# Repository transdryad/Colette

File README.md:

# Colette

A keyboard designed to be ergonomic, clean, convenient, maintainable, and versatile.
It is optimized for English, but can type every character supported by the US International layout (though it's not followed or fully required for basic usage.)
By default, it uses Colemak Mod-DH with a few changes to punctuation.

I made this keyboard to get more experience building hardware and enable a more cohesive coding environment.
I also wanted it to be good at typing text as well and have support for similar languages to english like French,
Spanish, and German.

* Keyboard Maintainer: [Hazel Viswanath](https://github.com/transdryad)
* Hardware Supported: Colette PCB, RPi/Orpheus Pico v1, Cherry MX keys, standard TRS jack

# Software used:
Kicad, Pycharm, FreeCAD, QMK, and Keyboard-Layout-Editor.com

# Firmware:
To compile & flash formware, install qmk system-wide and run bf.sh.
When it's "waiting for drive," plug in while pressing the BOOTSEL button on the PICO.
WARNING: the script will delete qmk firmware monorepo tree.
Backup any changes.

# BOM

BOM also in BOM.csv

| Part                      | Quantity | Proposed Sourcing?                                                                            |
|:--------------------------|:---------|:----------------------------------------------------------------------------------------------|
| PCBs                      | 2        | https://jlcpcb.com                                                                            |
| KeySwitches               | 58       | https://mechanicalkeyboards.com/products/cherry-mx2a-brown-55g-tactile?variant=48020838351148 |
| Keycaps                   | ~58      | https://www.amazon.com/YMDK-Profile-Keyset-Mechanical-Keyboard/dp/B07S18VCDN?th=1             |
| 1N4148 Diodes             | 58       | https://www.digikey.com/en/products/detail/onsemi/1N4148/458603                               |
| TRS Jacks                 | 2        | https://www.digikey.com/en/products/detail/same-sky-formerly-cui-devices/SJ1-3523N/738689     |
| TRS Cables                | 1        | https://www.mycablemart.com/store/cart.php?m=product_detail&p=9040                            |
| Orpheus Picos             | 2        | HQ?                                                                                           |
| M3x16mm Screws            | 8        | ?                                                                                             |
| M3x5mx4mm headset inserts | 8        | ?                                                                                             |
| Case                      | 4 parts  | Printing legion?                                                                              |

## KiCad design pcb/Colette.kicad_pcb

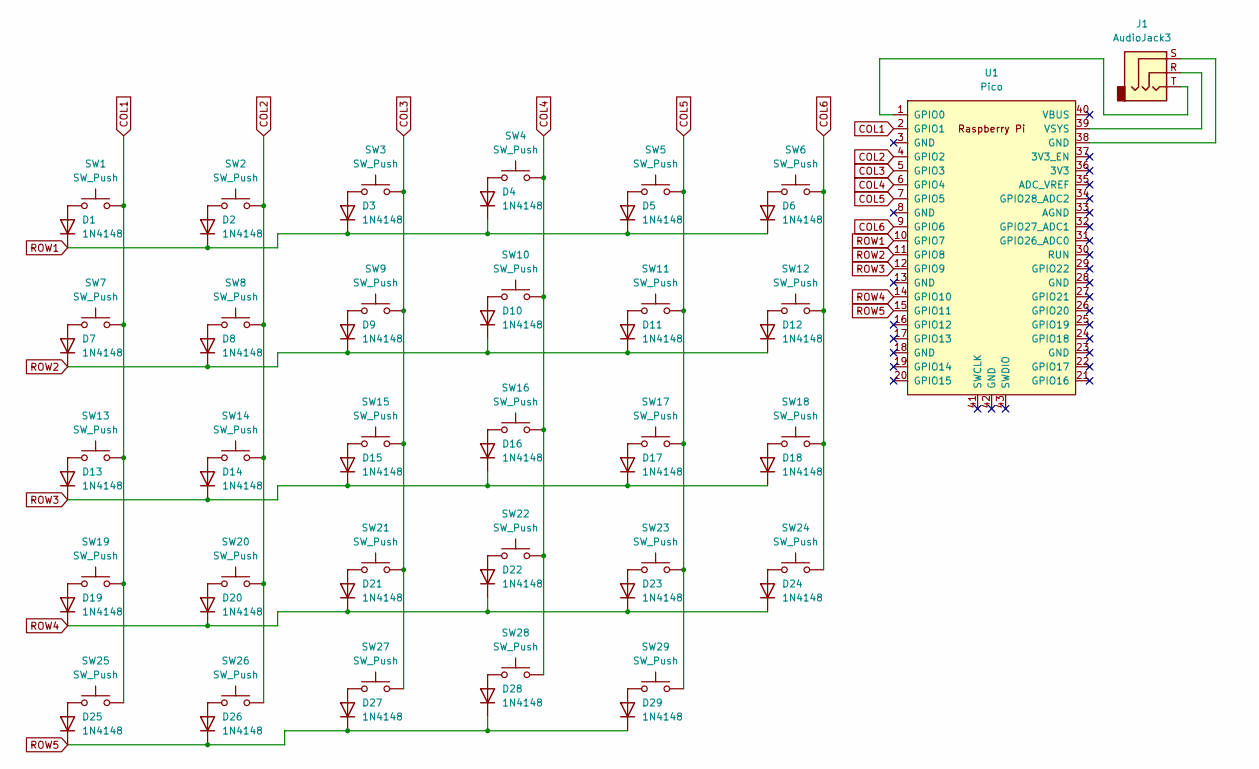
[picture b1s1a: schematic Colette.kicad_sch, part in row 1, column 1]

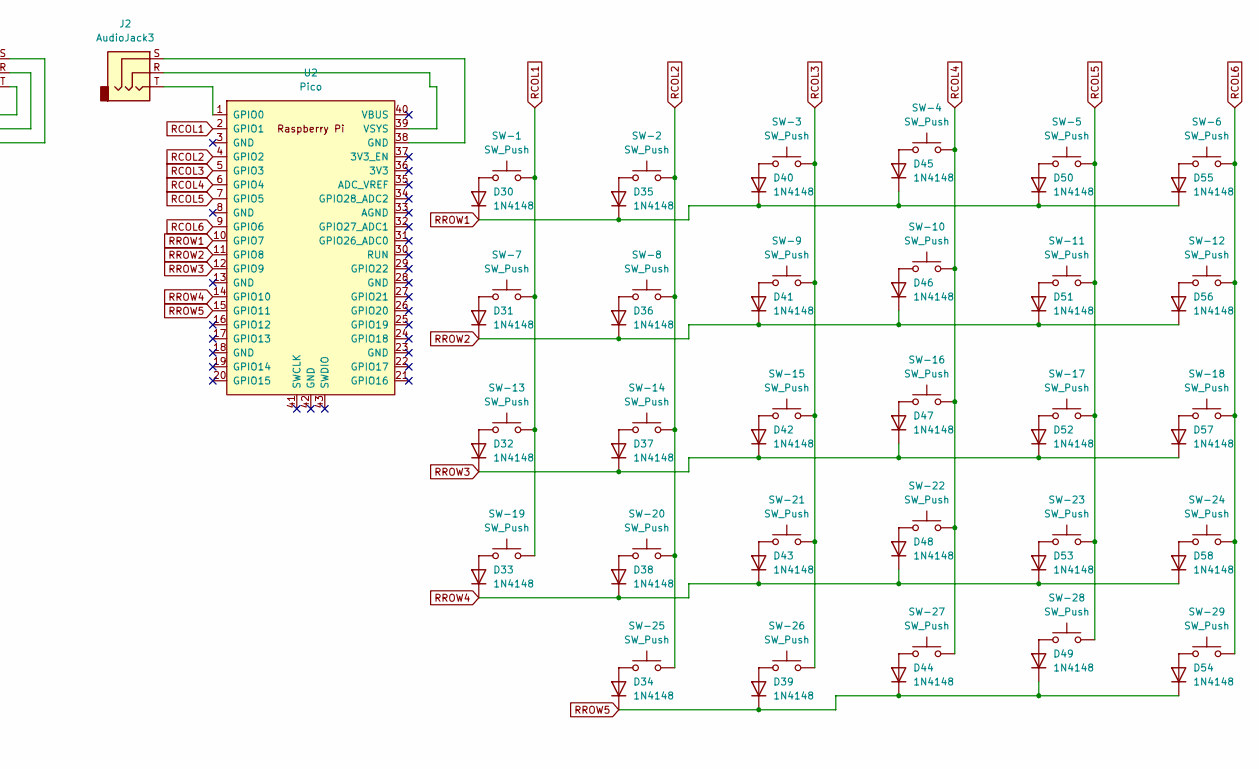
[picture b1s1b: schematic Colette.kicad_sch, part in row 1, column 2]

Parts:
D1, D2, D3, D4, D5, D6, D7, D8, D9, D10, D11, D12, D13, D14, D15, D16, D17, D18, D19, D20, D21, D22, D23, D24, D25, D26, D27, D28, D29, D30, D31, D32, D33, D34, D35, D36, D37, D38, D39, D40, D41, D42, D43, D44, D45, D46, D47, D48, D49, D50, D51, D52, D53, D54, D55, D56, D57, D58: 1N4148; D_DO-35_SOD27_P7.62mm_Horizontal
J1, J2: AudioJack3; Jack_3.5mm_CUI_SJ1-3523N_Horizontal
SW1, SW2, SW3, SW4, SW5, SW6, SW7, SW8, SW9, SW10, SW11, SW12, SW13, SW14, SW15, SW16, SW17, SW18, SW19, SW20, SW21, SW22, SW23, SW24, SW25, SW26, SW27, SW28: SW_Push; SW_Cherry_MX_1.00u_PCB
SW29: SW_Push; SW_Cherry_MX_2.00u_PCB
SW-1, SW-2, SW-3, SW-4, SW-5, SW-6, SW-7, SW-8, SW-9, SW-10, SW-11, SW-12, SW-13, SW-14, SW-15, SW-16, SW-17, SW-18, SW-19, SW-20, SW-21, SW-22, SW-23, SW-24, SW-26, SW-27, SW-28, SW-29: SW_Push; SW_Cherry_MX_1.00u_PCB
SW-25: SW_Push; SW_Cherry_MX_2.00u_PCB
U1, U2: Pico; RaspberryPi_Pico_Common_THT

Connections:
COL1: SW1.2, SW7.2, SW13.2, SW19.2, SW25.2, U1.2 (GPIO1)
COL2: SW2.2, SW8.2, SW14.2, SW20.2, SW26.2, U1.4 (GPIO2)
COL3: SW3.2, SW9.2, SW15.2, SW21.2, SW27.2, U1.5 (GPIO3)
COL4: SW4.2, SW10.2, SW16.2, SW22.2, SW28.2, U1.6 (GPIO4)
COL5: SW5.2, SW11.2, SW17.2, SW23.2, SW29.2, U1.7 (GPIO5)
COL6: SW6.2, SW12.2, SW18.2, SW24.2, U1.9 (GPIO6)
unnamed: D1.2 (A), SW1.1
unnamed: D2.2 (A), SW2.1
unnamed: D3.2 (A), SW3.1
unnamed: D4.2 (A), SW4.1
unnamed: D5.2 (A), SW5.1
unnamed: D6.2 (A), SW6.1
unnamed: D7.2 (A), SW7.1
unnamed: D8.2 (A), SW8.1
unnamed: D9.2 (A), SW9.1
unnamed: D10.2 (A), SW10.1
unnamed: D11.2 (A), SW11.1
unnamed: D12.2 (A), SW12.1
unnamed: D13.2 (A), SW13.1
unnamed: D14.2 (A), SW14.1
unnamed: D15.2 (A), SW15.1
unnamed: D16.2 (A), SW16.1
unnamed: D17.2 (A), SW17.1
unnamed: D18.2 (A), SW18.1
unnamed: D19.2 (A), SW19.1
unnamed: D20.2 (A), SW20.1
unnamed: D21.2 (A), SW21.1
unnamed: D22.2 (A), SW22.1
unnamed: D23.2 (A), SW23.1
unnamed: D24.2 (A), SW24.1
unnamed: D25.2 (A), SW25.1
unnamed: D26.2 (A), SW26.1
unnamed: D27.2 (A), SW27.1
unnamed: D28.2 (A), SW28.1
unnamed: D29.2 (A), SW29.1
unnamed: D30.2 (A), SW-1.1
unnamed: D31.2 (A), SW-7.1
unnamed: D32.2 (A), SW-13.1
unnamed: D33.2 (A), SW-19.1
unnamed: D34.2 (A), SW-25.1
unnamed: D35.2 (A), SW-2.1
unnamed: D36.2 (A), SW-8.1
unnamed: D37.2 (A), SW-14.1
unnamed: D38.2 (A), SW-20.1
unnamed: D39.2 (A), SW-26.1
unnamed: D40.2 (A), SW-3.1
unnamed: D41.2 (A), SW-9.1
unnamed: D42.2 (A), SW-15.1
unnamed: D43.2 (A), SW-21.1
unnamed: D44.2 (A), SW-27.1
unnamed: D45.2 (A), SW-4.1
unnamed: D46.2 (A), SW-10.1
unnamed: D47.2 (A), SW-16.1
unnamed: D48.2 (A), SW-22.1
unnamed: D49.2 (A), SW-28.1
unnamed: D50.2 (A), SW-5.1
unnamed: D51.2 (A), SW-11.1
unnamed: D52.2 (A), SW-17.1
unnamed: D53.2 (A), SW-23.1
unnamed: D54.2 (A), SW-29.1
unnamed: D55.2 (A), SW-6.1
unnamed: D56.2 (A), SW-12.1
unnamed: D57.2 (A), SW-18.1
unnamed: D58.2 (A), SW-24.1
unnamed: J1.S, U1.38 (GND)
unnamed: J2.S, U2.38 (GND)
unnamed: J1.T, U1.1 (GPIO0)
unnamed: J1.R, U1.39 (VSYS)
unnamed: J2.T, U2.1 (GPIO0)
unnamed: J2.R, U2.39 (VSYS)
RCOL1: SW-1.2, SW-7.2, SW-13.2, SW-19.2, U2.2 (GPIO1)
RCOL2: SW-2.2, SW-8.2, SW-14.2, SW-20.2, SW-25.2, U2.4 (GPIO2)
RCOL3: SW-3.2, SW-9.2, SW-15.2, SW-21.2, SW-26.2, U2.5 (GPIO3)
RCOL4: SW-4.2, SW-10.2, SW-16.2, SW-22.2, SW-27.2, U2.6 (GPIO4)
RCOL5: SW-5.2, SW-11.2, SW-17.2, SW-23.2, SW-28.2, U2.7 (GPIO5)
RCOL6: SW-6.2, SW-12.2, SW-18.2, SW-24.2, SW-29.2, U2.9 (GPIO6)
ROW1: D1.1 (K), D2.1 (K), D3.1 (K), D4.1 (K), D5.1 (K), D6.1 (K), U1.10 (GPIO7)
ROW2: D7.1 (K), D8.1 (K), D9.1 (K), D10.1 (K), D11.1 (K), D12.1 (K), U1.11 (GPIO8)
ROW3: D13.1 (K), D14.1 (K), D15.1 (K), D16.1 (K), D17.1 (K), D18.1 (K), U1.12 (GPIO9)
ROW4: D19.1 (K), D20.1 (K), D21.1 (K), D22.1 (K), D23.1 (K), D24.1 (K), U1.14 (GPIO10)
ROW5: D25.1 (K), D26.1 (K), D27.1 (K), D28.1 (K), D29.1 (K), U1.15 (GPIO11)
RROW1: D30.1 (K), D35.1 (K), D40.1 (K), D45.1 (K), D50.1 (K), D55.1 (K), U2.10 (GPIO7)
RROW2: D31.1 (K), D36.1 (K), D41.1 (K), D46.1 (K), D51.1 (K), D56.1 (K), U2.11 (GPIO8)
RROW3: D32.1 (K), D37.1 (K), D42.1 (K), D47.1 (K), D52.1 (K), D57.1 (K), U2.12 (GPIO9)
RROW4: D33.1 (K), D38.1 (K), D43.1 (K), D48.1 (K), D53.1 (K), D58.1 (K), U2.14 (GPIO10)
RROW5: D34.1 (K), D39.1 (K), D44.1 (K), D49.1 (K), D54.1 (K), U2.15 (GPIO11)

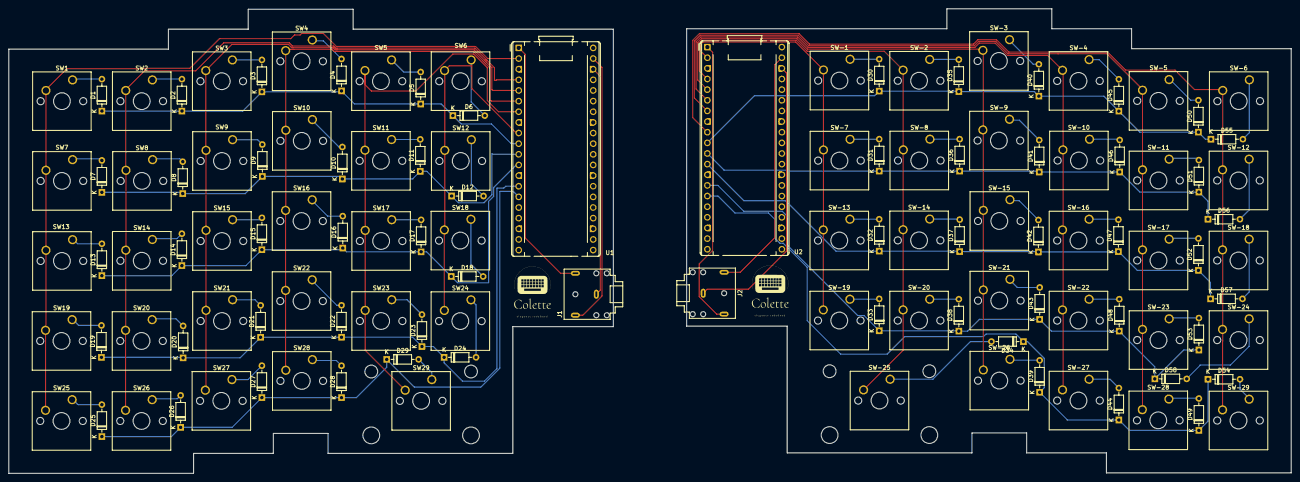
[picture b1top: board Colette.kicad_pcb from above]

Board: 2 copper layers, 306.1 x 110.9 mm, 120 parts (0 on the bottom side), 86 nets.

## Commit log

2025-05-24 add files
2025-05-24 do some documentation, nondestructive build
2025-05-24 SPDX
2025-05-24 Create LICENSE
2025-06-05 Pretty much there? may need to separate pcbs.
2025-06-05 BOM in csv.
